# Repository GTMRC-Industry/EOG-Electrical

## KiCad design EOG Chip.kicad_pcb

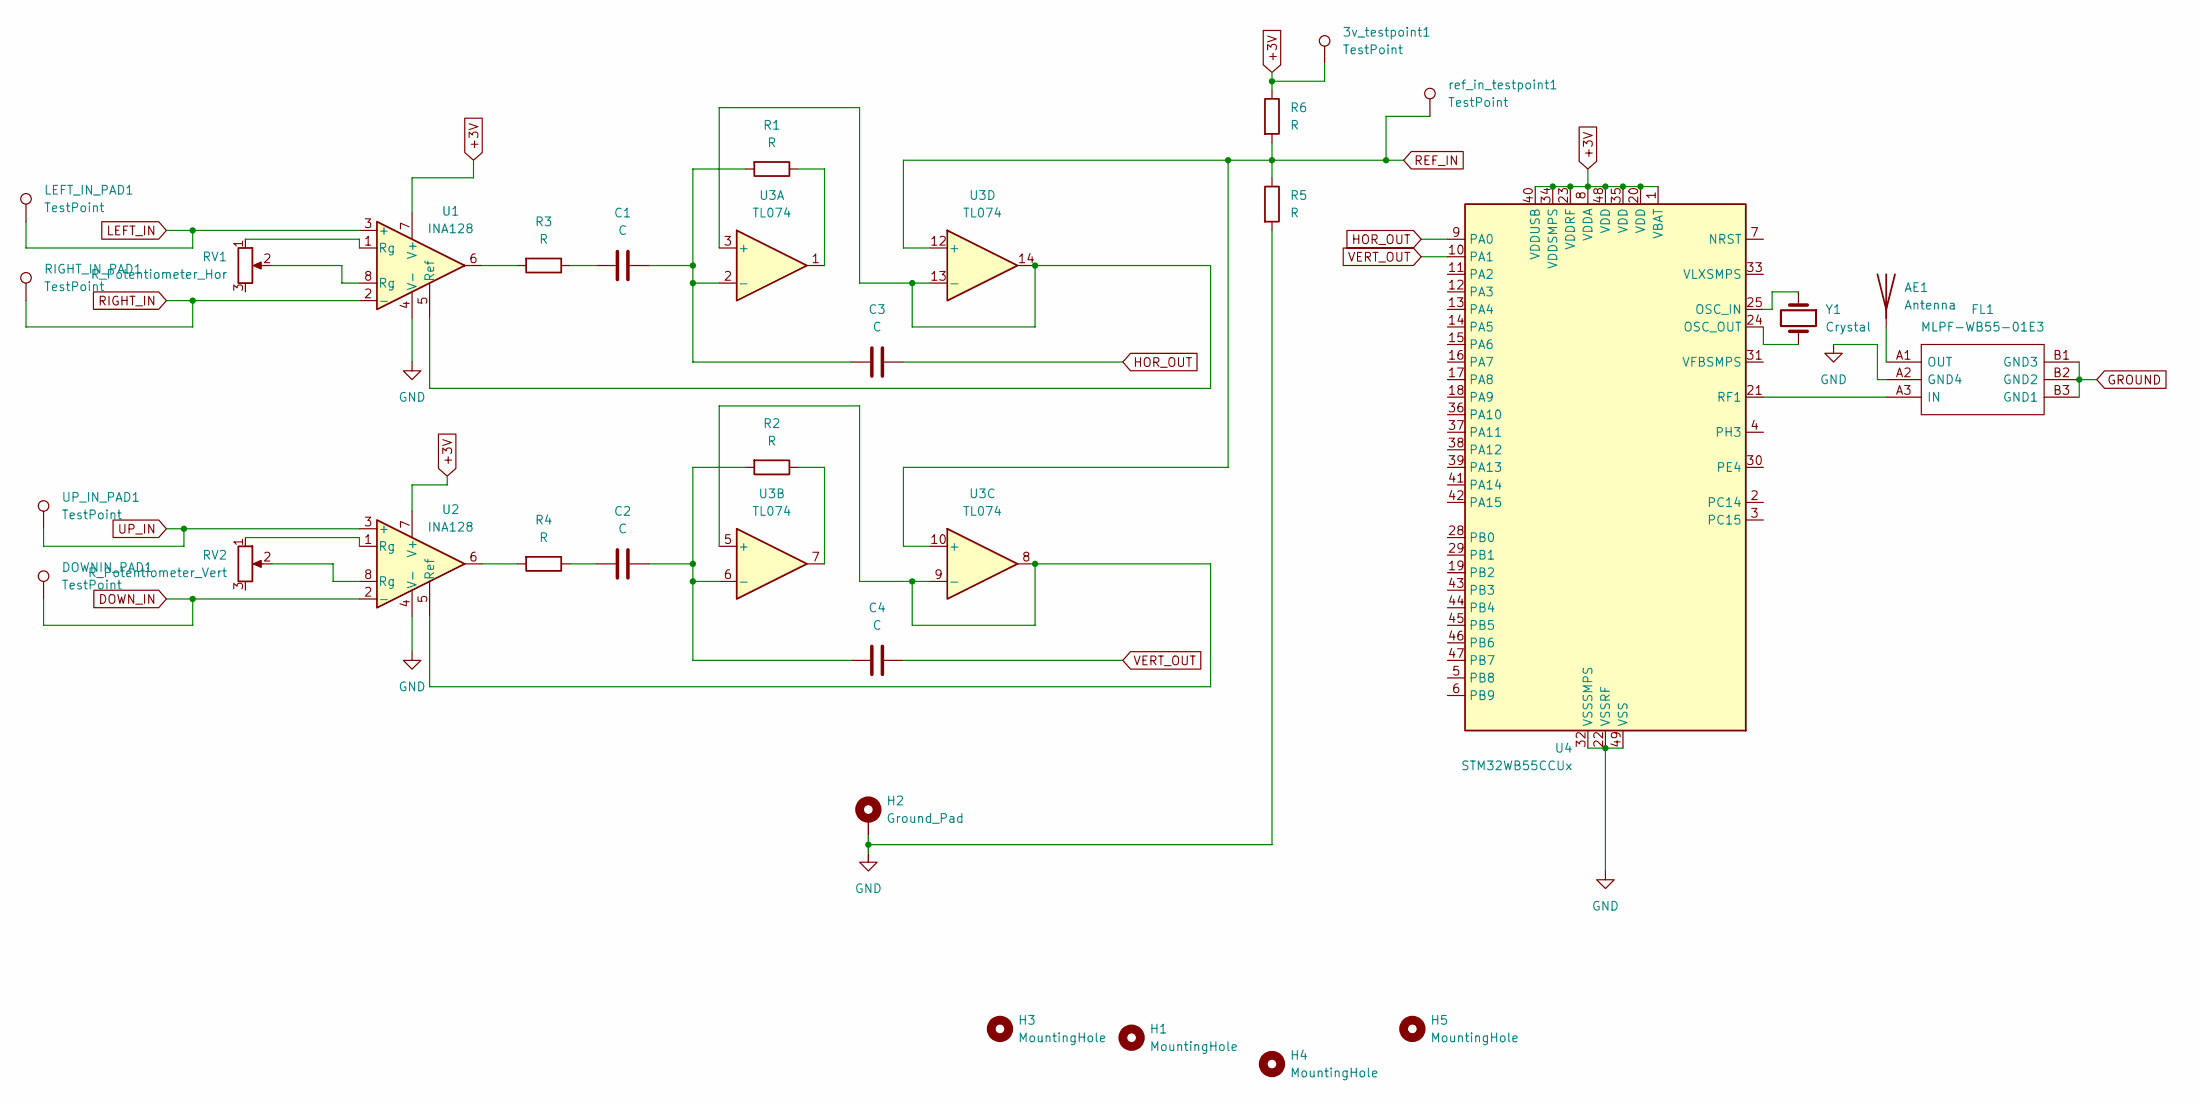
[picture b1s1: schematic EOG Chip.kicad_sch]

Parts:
3v_testpoint1: TestPoint; TestPoint_Pad_1.0x1.0mm
AE1: Antenna; ANTC3216X60N
C1, C2, C3, C4: C; C_0603_1608Metric
DOWNIN_PAD1: TestPoint; TestPoint_Pad_1.0x1.0mm
FL1: MLPF-WB55-01E3; BUMPLESS_CSP_2025; Manufacturer_Part_Number MLPF-WB55-01E3; Mouser Part Number 511-MLPF-WB55-01E3
H1, H3, H4, H5: MountingHole; MountingHole_2mm
H2: Ground_Pad; MountingHole_2.2mm_M2_DIN965_Pad
LEFT_IN_PAD1: TestPoint; TestPoint_Pad_1.0x1.0mm
R1, R2, R3, R4, R5, R6: R; R_0603_1608Metric
RIGHT_IN_PAD1: TestPoint; TestPoint_Pad_1.0x1.0mm
RV1: R_Potentiometer_Hor; TSM41YJ503KR05
RV2: R_Potentiometer_Vert; TSM41YJ503KR05
U1, U2: INA128; SOP65P490X110-8N
U3: TL074; SOIC127P600X175-14N
U4: STM32WB55CCUx; QFN-48-1EP_7x7mm_P0.5mm_EP5.6x5.6mm
UP_IN_PAD1: TestPoint; TestPoint_Pad_1.0x1.0mm
Y1: Crystal; ABM11A32000MHZD2YT3
ref_in_testpoint1: TestPoint; TestPoint_Pad_1.0x1.0mm

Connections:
+3V: 3v_testpoint1.1, R6.1, U1.7 (V+), U2.7 (V+), U4.1 (VBAT), U4.8 (VDDA), U4.20 (VDD), U4.23 (VDDRF), U4.34 (VDDSMPS), U4.35 (VDD), U4.40 (VDDUSB), U4.48 (VDD)
DOWN_IN: DOWNIN_PAD1.1, U2.2 (-)
GND: FL1.A2 (GND4), H2.1, R5.2, U1.4 (V-), U2.4 (V-), U4.22 (VSSRF), U4.32 (VSSSMPS), U4.49 (VSS)
GROUND: FL1.B1 (GND3), FL1.B2 (GND2), FL1.B3 (GND1)
HOR_OUT: C3.2, U4.9 (PA0)
LEFT_IN: LEFT_IN_PAD1.1, U1.3 (+)
unnamed: AE1.1 (A), FL1.A1 (OUT)
unnamed: C1.1, R3.1
unnamed: C2.1, R4.1
unnamed: FL1.A3 (IN), U4.21 (RF1)
unnamed: R1.1, U3.1
unnamed: R2.1, U3.7
unnamed: R3.2, U1.6
unnamed: R4.2, U2.6
unnamed: RV1.1, U1.1 (Rg)
unnamed: RV1.2, U1.8 (Rg)
unnamed: RV2.1, U2.1 (Rg)
unnamed: RV2.2, U2.8 (Rg)
unnamed: U1.5 (Ref), U3.3 (+), U3.13 (-), U3.14
unnamed: U2.5 (Ref), U3.5 (+), U3.8, U3.9 (-)
unnamed: C1.2, C3.1, R1.2, U3.2 (-)
unnamed: C2.2, C4.1, R2.2, U3.6 (-)
unnamed: U4.25 (OSC_IN), Y1.1
unnamed: U4.24 (OSC_OUT), Y1.2
REF_IN: R5.1, R6.2, U3.10 (+), U3.12 (+), ref_in_testpoint1.1
RIGHT_IN: RIGHT_IN_PAD1.1, U1.2 (-)
UP_IN: U2.3 (+), UP_IN_PAD1.1
VERT_OUT: C4.2, U4.10 (PA1)

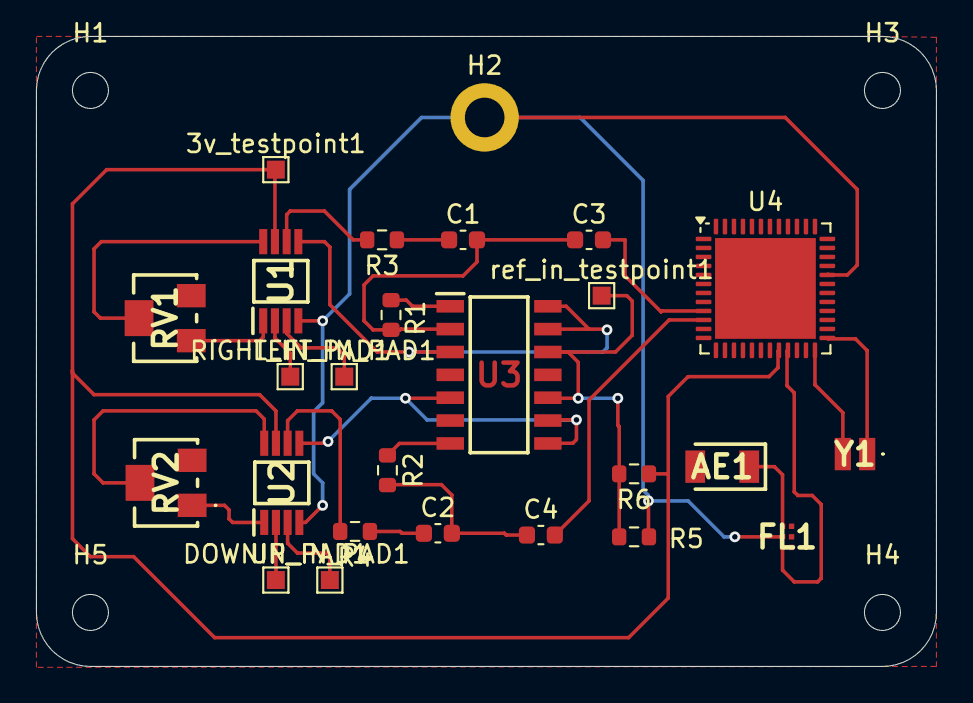
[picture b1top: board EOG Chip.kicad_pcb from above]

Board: 2 copper layers, 50.0 x 35.0 mm, 30 parts (0 on the bottom side), 28 nets.

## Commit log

2025-10-09 Added microcontroller and antenna
2025-10-09 added datasheets and references
2025-10-09 added folder for datasheets and references
2025-10-09 add datasheets to datasheet folder
2025-10-20 Added footprints for antenna filter module and microcontroller
2025-10-27 updated files
2025-10-27 updating schematics
2025-10-27 added footprints.zip
2025-11-07 Added potentiometers and started on traces
2025-11-14 updated schematic and pcb
    traces are almost finished
2025-11-14 updated pcb and schematic
